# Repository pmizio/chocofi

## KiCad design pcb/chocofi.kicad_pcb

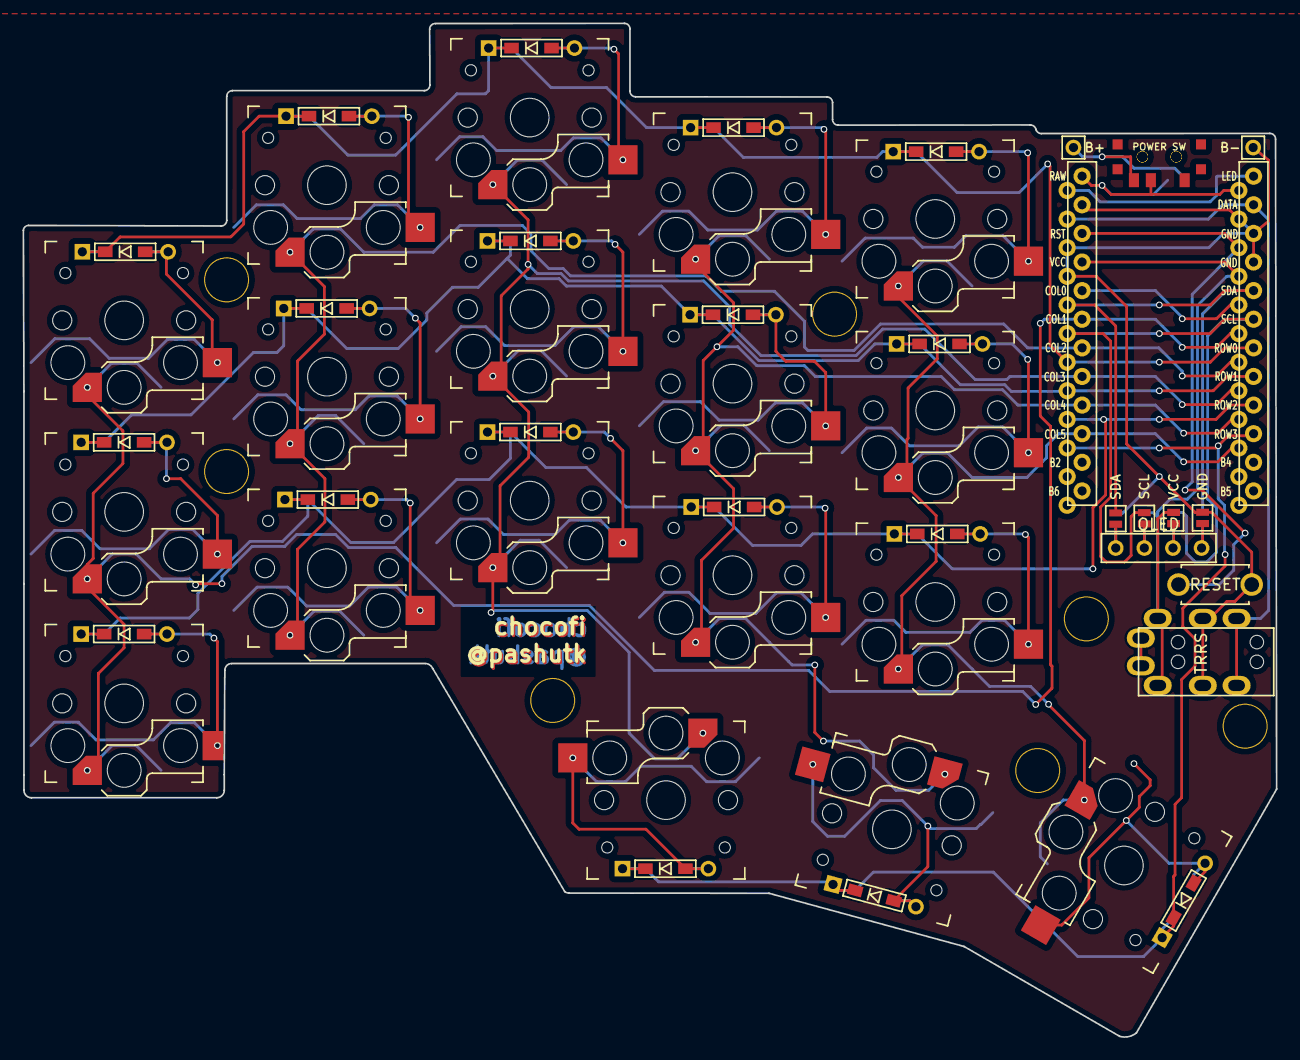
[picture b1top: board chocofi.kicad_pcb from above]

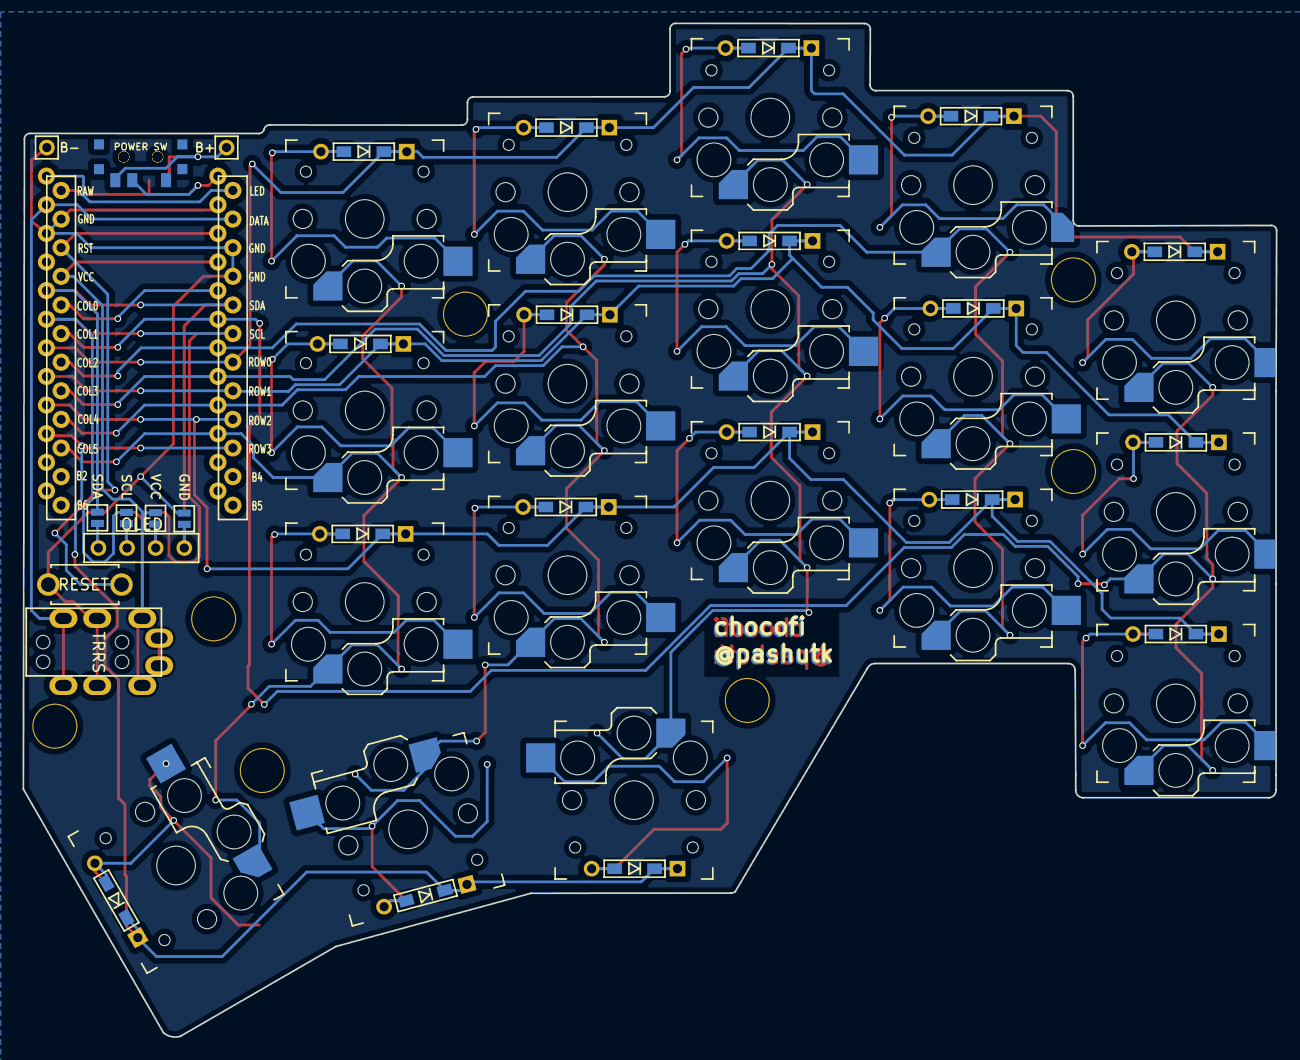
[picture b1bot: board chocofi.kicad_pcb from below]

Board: 2 copper layers, 111.3 x 90.0 mm, 59 parts (5 on the bottom side), 39 nets.

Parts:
B+: MountingHole_Pad; 1pin_conn
B-: MountingHole_Pad; 1pin_conn
D2, D3, D4, D5, D6, D8, D9, D10, D11, D12, D14, D15, D16, D17, D18, D19, D20, D21: D; D3_TH_SMD
H1: h1; LEGO_HOLE
J1: MJ-4PP-9
J2: OLED
JP6, JP61: SDA; Jumper
JP62, JP68: GND; Jumper
JP63, JP66: SCL; Jumper
JP64, JP65: VCC; Jumper
POWER SW: SW_SPDT; SPDT_C128955
POWER SW#2: SW_SPDT; SPDT_C128955
RSW1: Val**; ResetSW
SW2, SW3, SW4, SW5, SW6, SW8, SW9, SW10, SW11, SW12, SW14, SW15, SW16, SW17, SW18, SW19, SW20, SW21: SW_PUSH; Kailh_socket_PG1350_reversible
U1: ProMicro; ProMicro_v2
h2: h2; LEGO_HOLE
h3: h3; LEGO_HOLE
h4: h4; LEGO_HOLE
h5: h5; LEGO_HOLE
h6: h6; LEGO_HOLE
h7: h7; LEGO_HOLE

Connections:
GND: B-.1, J1.C, JP62.1, JP68.1, RSW1.1, U1.3, U1.4, U1.23
unnamed: D2.2, SW2.2
unnamed: D3.2, SW3.2
unnamed: D4.2, SW4.2
unnamed: D5.2, SW5.2
unnamed: D6.2, SW6.2
unnamed: D8.2, SW8.2
unnamed: D9.2, SW9.2
unnamed: D10.2, SW10.2
unnamed: D11.2, SW11.2
unnamed: D12.2, SW12.2
unnamed: D14.2, SW14.2
unnamed: D15.2, SW15.2
unnamed: D16.2, SW16.2
unnamed: D17.2, SW17.2
unnamed: D18.2, SW18.2
unnamed: D19.2, SW19.2
unnamed: D20.2, SW20.2
unnamed: D21.2, SW21.2
unnamed: J2.3, JP65.2, JP66.2
unnamed: J2.4, JP6.2, JP68.2
unnamed: J2.2, JP63.2, JP64.2
unnamed: J2.1, JP61.2, JP62.2
unnamed: POWER SW.2, POWER SW#2.2, U1.24
SCL: JP63.1, JP66.1, U1.6
SDA: JP6.1, JP61.1, U1.5
VCC: J1.D, JP64.1, JP65.1, U1.21
bat+: B+.1, POWER SW.3, POWER SW#2.3
col1: SW2.1, SW8.1, SW14.1, U1.19
col2: SW3.1, SW9.1, SW15.1, U1.18
col3: SW4.1, SW10.1, SW16.1, SW19.1, U1.17
col4: SW5.1, SW11.1, SW17.1, SW20.1, U1.16
col5: SW6.1, SW12.1, SW18.1, SW21.1, U1.15
data: J1.B, U1.2
reset: RSW1.2, U1.22
row0: D2.1, D3.1, D4.1, D5.1, D6.1, U1.7
row1: D8.1, D9.1, D10.1, D11.1, D12.1, U1.8
row2: D14.1, D15.1, D16.1, D17.1, D18.1, U1.9
row3: D19.1, D20.1, D21.1, U1.10

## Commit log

2023-01-07 feat: sandwich case mod
2023-01-07 chore: update files
2023-01-07 fix: bottom plate not don't cover entire pcb
2023-01-07 chore: update bottom plate
2023-01-27 feat: add reversable switch
